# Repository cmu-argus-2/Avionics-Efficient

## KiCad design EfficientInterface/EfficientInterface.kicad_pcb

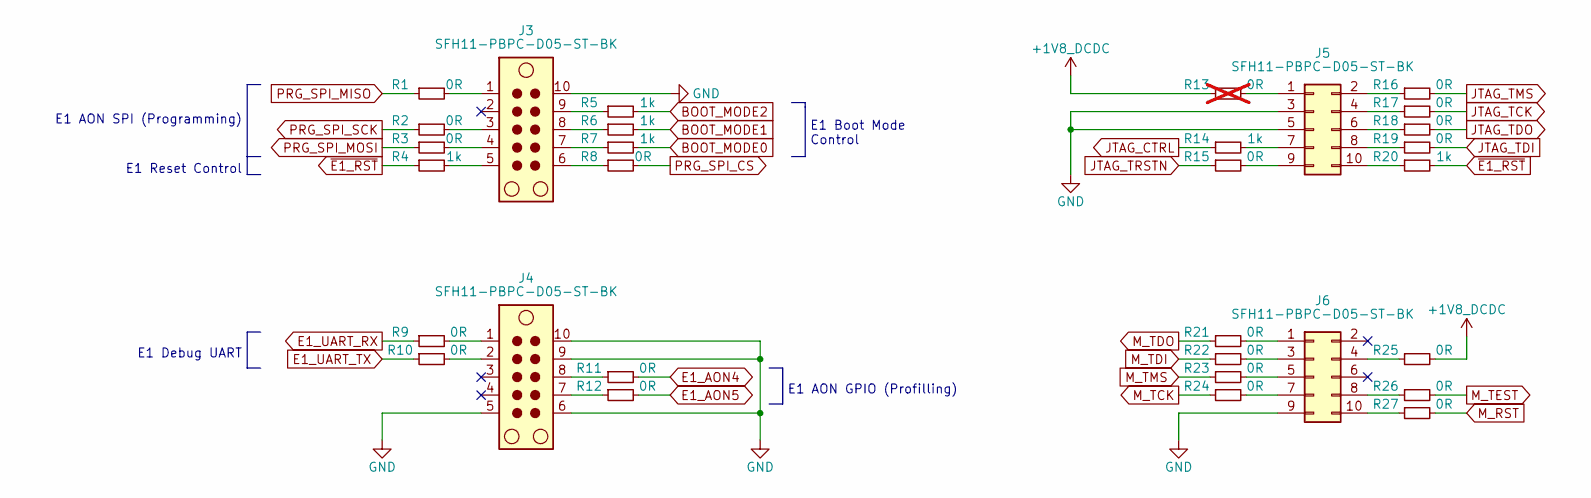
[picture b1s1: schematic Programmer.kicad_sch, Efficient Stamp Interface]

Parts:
J3, J4, J5, J6: SFH11-PBPC-D05-ST-BK; PinSocket_2x05_P2.54mm_Vertical
R1, R2, R3, R8, R9, R10, R11, R12, R15, R16, R17, R18, R19, R21, R22, R23, R24, R25, R26, R27: 0R; R_0603_1608Metric
R4, R5, R6, R7, R14, R20: 1k; R_0603_1608Metric
R13: 0R; R_0603_1608Metric; not fitted

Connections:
+1V8_DCDC: R13.1, R25.2; also elsewhere on the board
BOOT_MODE0: R7.2; also elsewhere on the board
BOOT_MODE1: R6.2; also elsewhere on the board
BOOT_MODE2: R5.2; also elsewhere on the board
DIGIO034_B: R10.1; also elsewhere on the board
DIGIO035_B: R9.1; also elsewhere on the board
E1_AON4: R11.2; also elsewhere on the board
E1_AON5: R12.2; also elsewhere on the board
GND: J3.10, J4.5, J4.6, J4.9, J4.10, J5.3, J5.5, J6.9; also elsewhere on the board
JTAG_CTRL: R14.1; also elsewhere on the board
JTAG_TCK: R17.2; also elsewhere on the board
JTAG_TDI: R19.2; also elsewhere on the board
JTAG_TDO: R18.2; also elsewhere on the board
JTAG_TMS: R16.2; also elsewhere on the board
JTAG_TRSTN: R15.1; also elsewhere on the board
M_RST: R27.2; also elsewhere on the board
M_TCK: R24.1; also elsewhere on the board
M_TDI: R22.1; also elsewhere on the board
M_TDO: R21.1; also elsewhere on the board
M_TEST: R26.2; also elsewhere on the board
M_TMS: R23.1; also elsewhere on the board
unnamed: J3.1, R1.2
unnamed: J3.3, R2.2
unnamed: J3.4, R3.2
unnamed: J3.5, R4.2
unnamed: J3.6, R8.1
unnamed: J3.7, R7.1
unnamed: J3.8, R6.1
unnamed: J3.9, R5.1
unnamed: J4.1, R9.2
unnamed: J4.2, R10.2
unnamed: J4.7, R12.1
unnamed: J4.8, R11.1
unnamed: J5.1, R13.2
unnamed: J5.2, R16.1
unnamed: J5.4, R17.1
unnamed: J5.6, R18.1
unnamed: J5.7, R14.2
unnamed: J5.8, R19.1
unnamed: J5.9, R15.2
unnamed: J5.10, R20.1
unnamed: J6.1, R21.2
unnamed: J6.3, R22.2
unnamed: J6.4, R25.1
unnamed: J6.5, R23.2
unnamed: J6.7, R24.2
unnamed: J6.8, R26.1
unnamed: J6.10, R27.1
PRG_SPI_CS: R8.2; also elsewhere on the board
PRG_SPI_MISO: R1.1; also elsewhere on the board
PRG_SPI_MOSI: R3.1; also elsewhere on the board
PRG_SPI_SCK: R2.1; also elsewhere on the board
~E1_RST: R4.1, R20.2; also elsewhere on the board

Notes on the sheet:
E1 Boot Mode Control
E1 AON SPI (Programming)
E1 AON GPIO (Profilling)
E1 Reset Control
E1 Debug UART

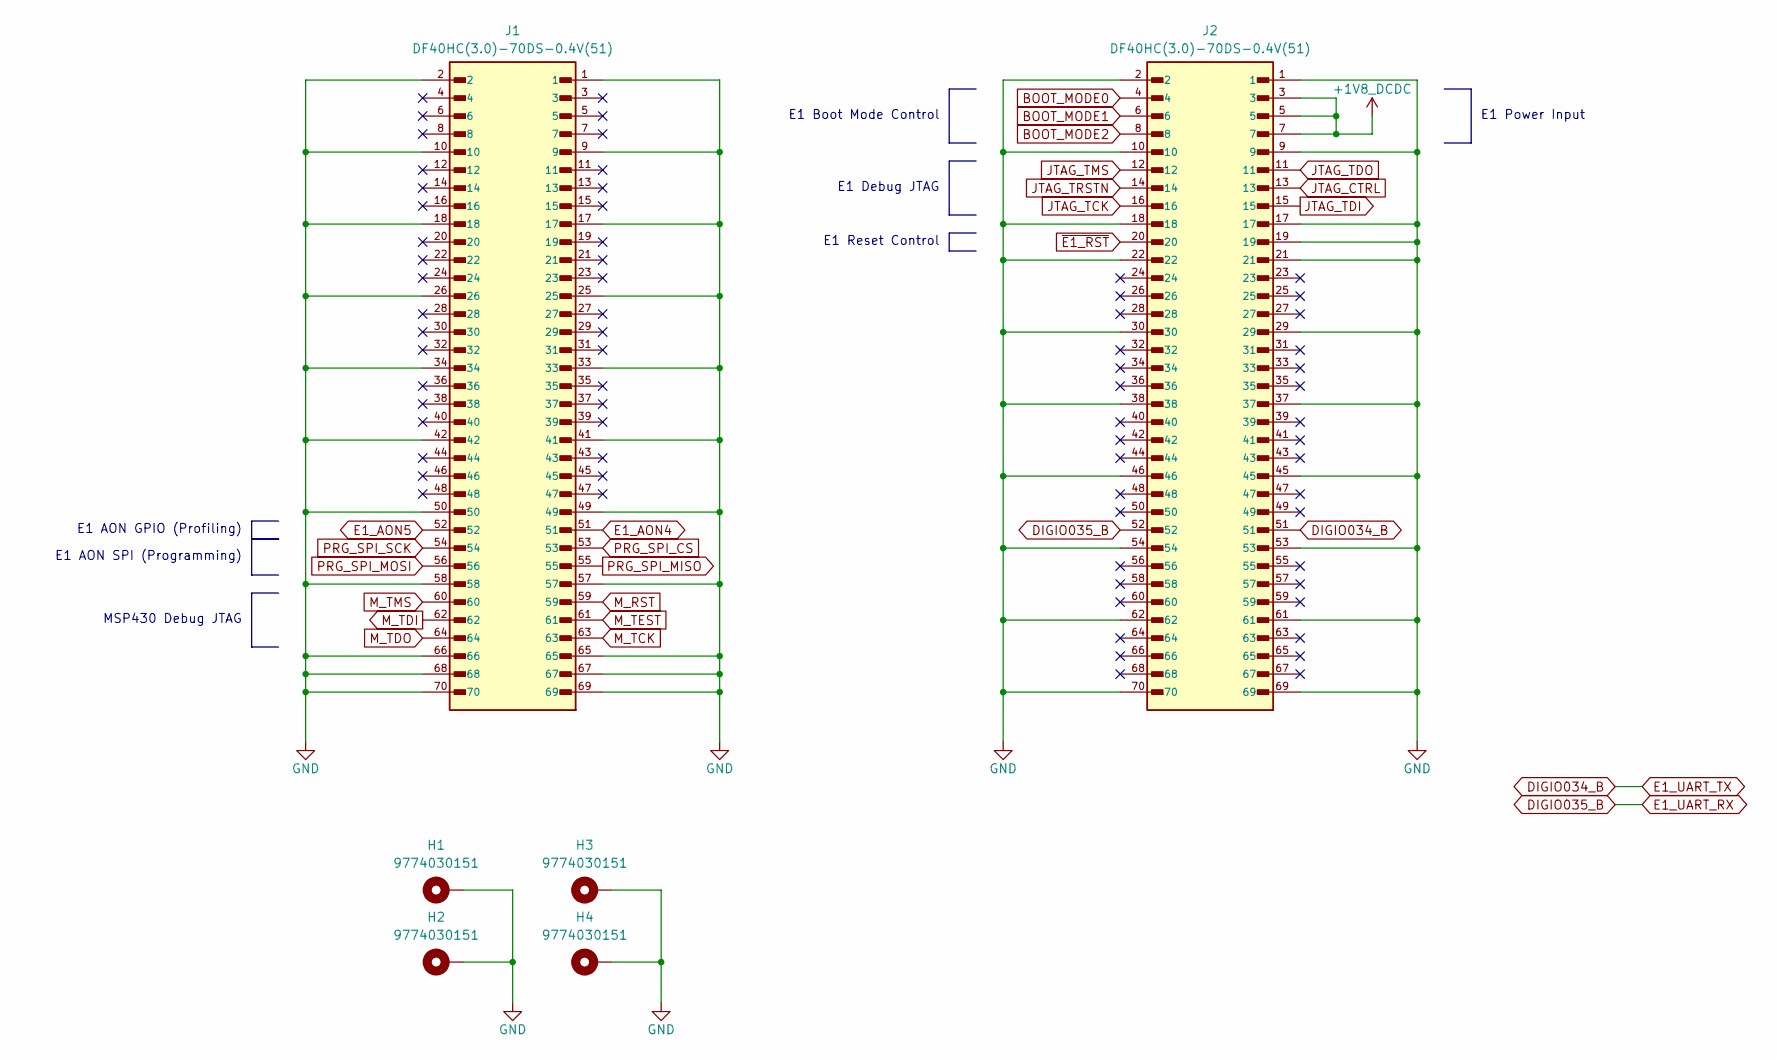
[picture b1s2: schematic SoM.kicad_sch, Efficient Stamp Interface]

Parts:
H1, H2, H3, H4: 9774030151; Mounting_Wuerth_WA-SMSI-M2.5_H3mm_9774030151
J1, J2: DF40HC(3.0)-70DS-0.4V(51); Hirose_DF40C-70DS-0.4V_2x35_P0.4mm

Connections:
+1V8_DCDC: J2.3, J2.5, J2.7; also elsewhere on the board
BOOT_MODE0: J2.4; also elsewhere on the board
BOOT_MODE1: J2.6; also elsewhere on the board
BOOT_MODE2: J2.8; also elsewhere on the board
DIGIO034_B: J2.51; also elsewhere on the board
DIGIO035_B: J2.52; also elsewhere on the board
E1_AON4: J1.51; also elsewhere on the board
E1_AON5: J1.52; also elsewhere on the board
GND: H1.1 (1_1), H2.1 (1_1), H3.1 (1_1), H4.1 (1_1), J1.1, J1.2, J1.9, J1.10, J1.17, J1.18, J1.25, J1.26, J1.33, J1.34, J1.41, J1.42, J1.49, J1.50, J1.57, J1.58, J1.65, J1.66, J1.67, J1.68, J1.69, J1.70, J2.1, J2.2, J2.9, J2.10, J2.17, J2.18, J2.19, J2.21, J2.22, J2.29, J2.30, J2.37, J2.38, J2.45, J2.46, J2.53, J2.54, J2.61, J2.62, J2.69, J2.70; also elsewhere on the board
JTAG_CTRL: J2.13; also elsewhere on the board
JTAG_TCK: J2.16; also elsewhere on the board
JTAG_TDI: J2.15; also elsewhere on the board
JTAG_TDO: J2.11; also elsewhere on the board
JTAG_TMS: J2.12; also elsewhere on the board
JTAG_TRSTN: J2.14; also elsewhere on the board
M_RST: J1.59; also elsewhere on the board
M_TCK: J1.63; also elsewhere on the board
M_TDI: J1.62; also elsewhere on the board
M_TDO: J1.64; also elsewhere on the board
M_TEST: J1.61; also elsewhere on the board
M_TMS: J1.60; also elsewhere on the board
PRG_SPI_CS: J1.53; also elsewhere on the board
PRG_SPI_MISO: J1.55; also elsewhere on the board
PRG_SPI_MOSI: J1.56; also elsewhere on the board
PRG_SPI_SCK: J1.54; also elsewhere on the board
~E1_RST: J2.20; also elsewhere on the board

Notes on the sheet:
E1 AON SPI (Programming)
E1 Boot Mode Control
E1 Reset Control
E1 AON GPIO (Profiling)
E1 Debug JTAG
MSP430 Debug JTAG
E1 Power Input

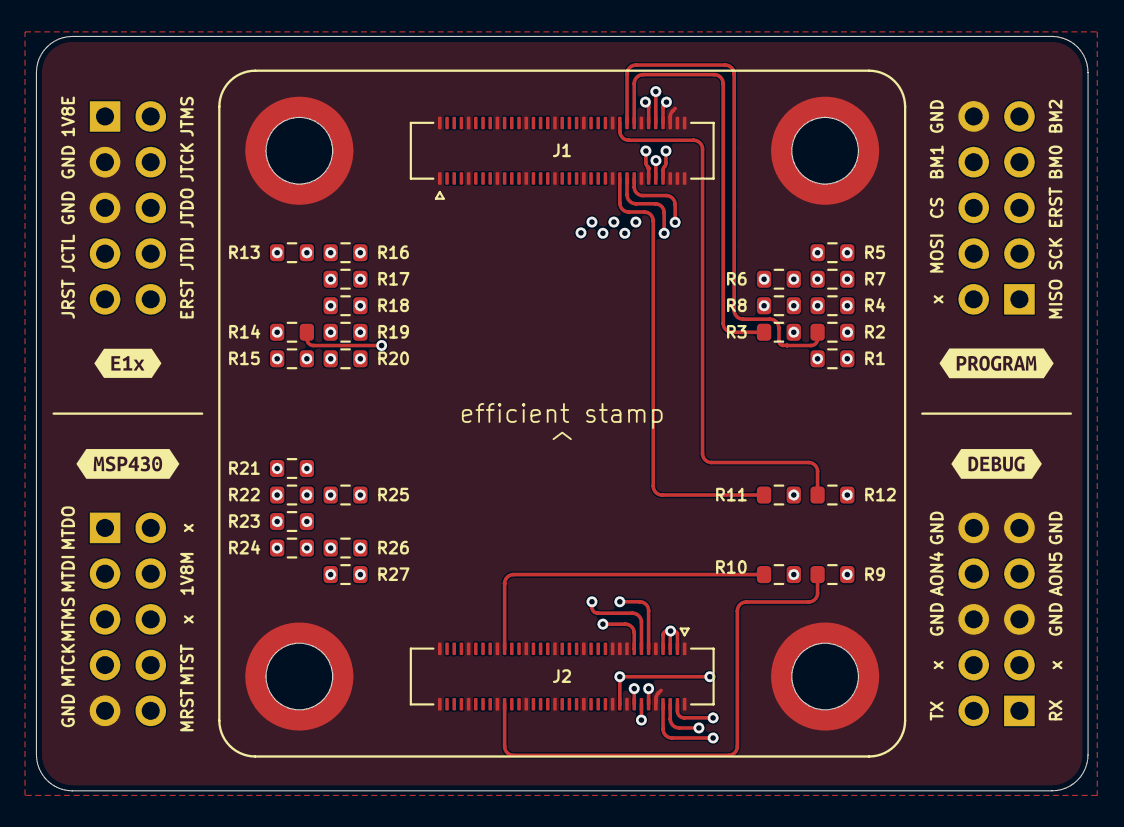
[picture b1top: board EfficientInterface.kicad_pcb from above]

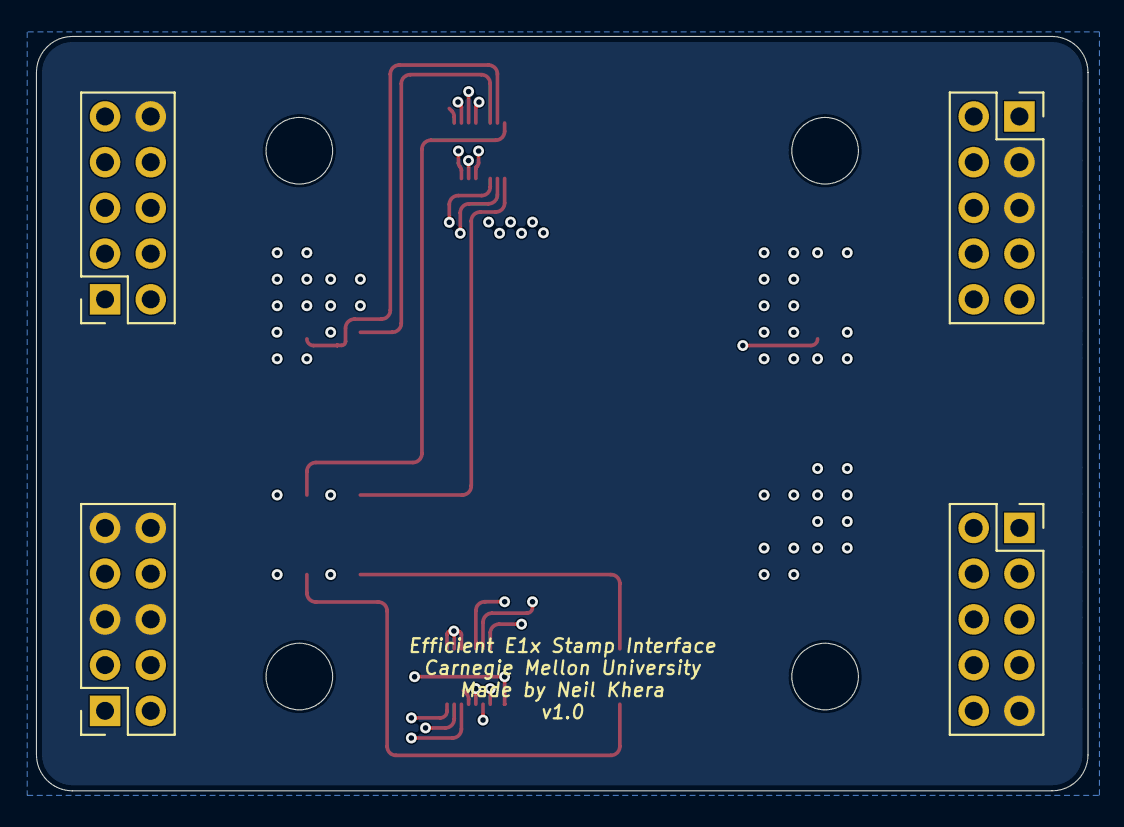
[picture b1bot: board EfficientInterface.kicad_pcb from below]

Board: 4 copper layers, 58.4 x 41.9 mm, 41 parts (4 on the bottom side), 53 nets.

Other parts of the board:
kibuzzard-6A03C779: G***; kibuzzard-6A03C779
kibuzzard-6A03E4CB: G***; kibuzzard-6A03E4CB
kibuzzard-6A03EEF0: G***; kibuzzard-6A03EEF0
kibuzzard-6A0274B3: G***; kibuzzard-6A0274B3

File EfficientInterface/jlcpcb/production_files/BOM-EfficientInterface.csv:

Comment,Designator,Footprint,LCSC,Quantity
0R,"R1,R10,R11,R12,R15,R16,R17,R18,R19,R2,R21,R22,R23,R24,R25,R26,R27,R3,R8,R9",R_0603_1608Metric,C2441282,20
1k,"R14,R20,R4,R5,R6,R7",R_0603_1608Metric,C2484691,6
DF40HC(3.0)-70DS-0.4V(51),"J1,J2",Hirose_DF40C-70DS-0.4V_2x35_P0.4mm,C597944,2
SFH11-PBPC-D05-ST-BK,J3,PinSocket_2x05_P2.54mm_Vertical,,1
SFH11-PBPC-D05-ST-BK,J5,PinSocket_2x05_P2.54mm_Vertical,,1
SFH11-PBPC-D05-ST-BK,J6,PinSocket_2x05_P2.54mm_Vertical,,1
SFH11-PBPC-D05-ST-BK,J4,PinSocket_2x05_P2.54mm_Vertical,,1

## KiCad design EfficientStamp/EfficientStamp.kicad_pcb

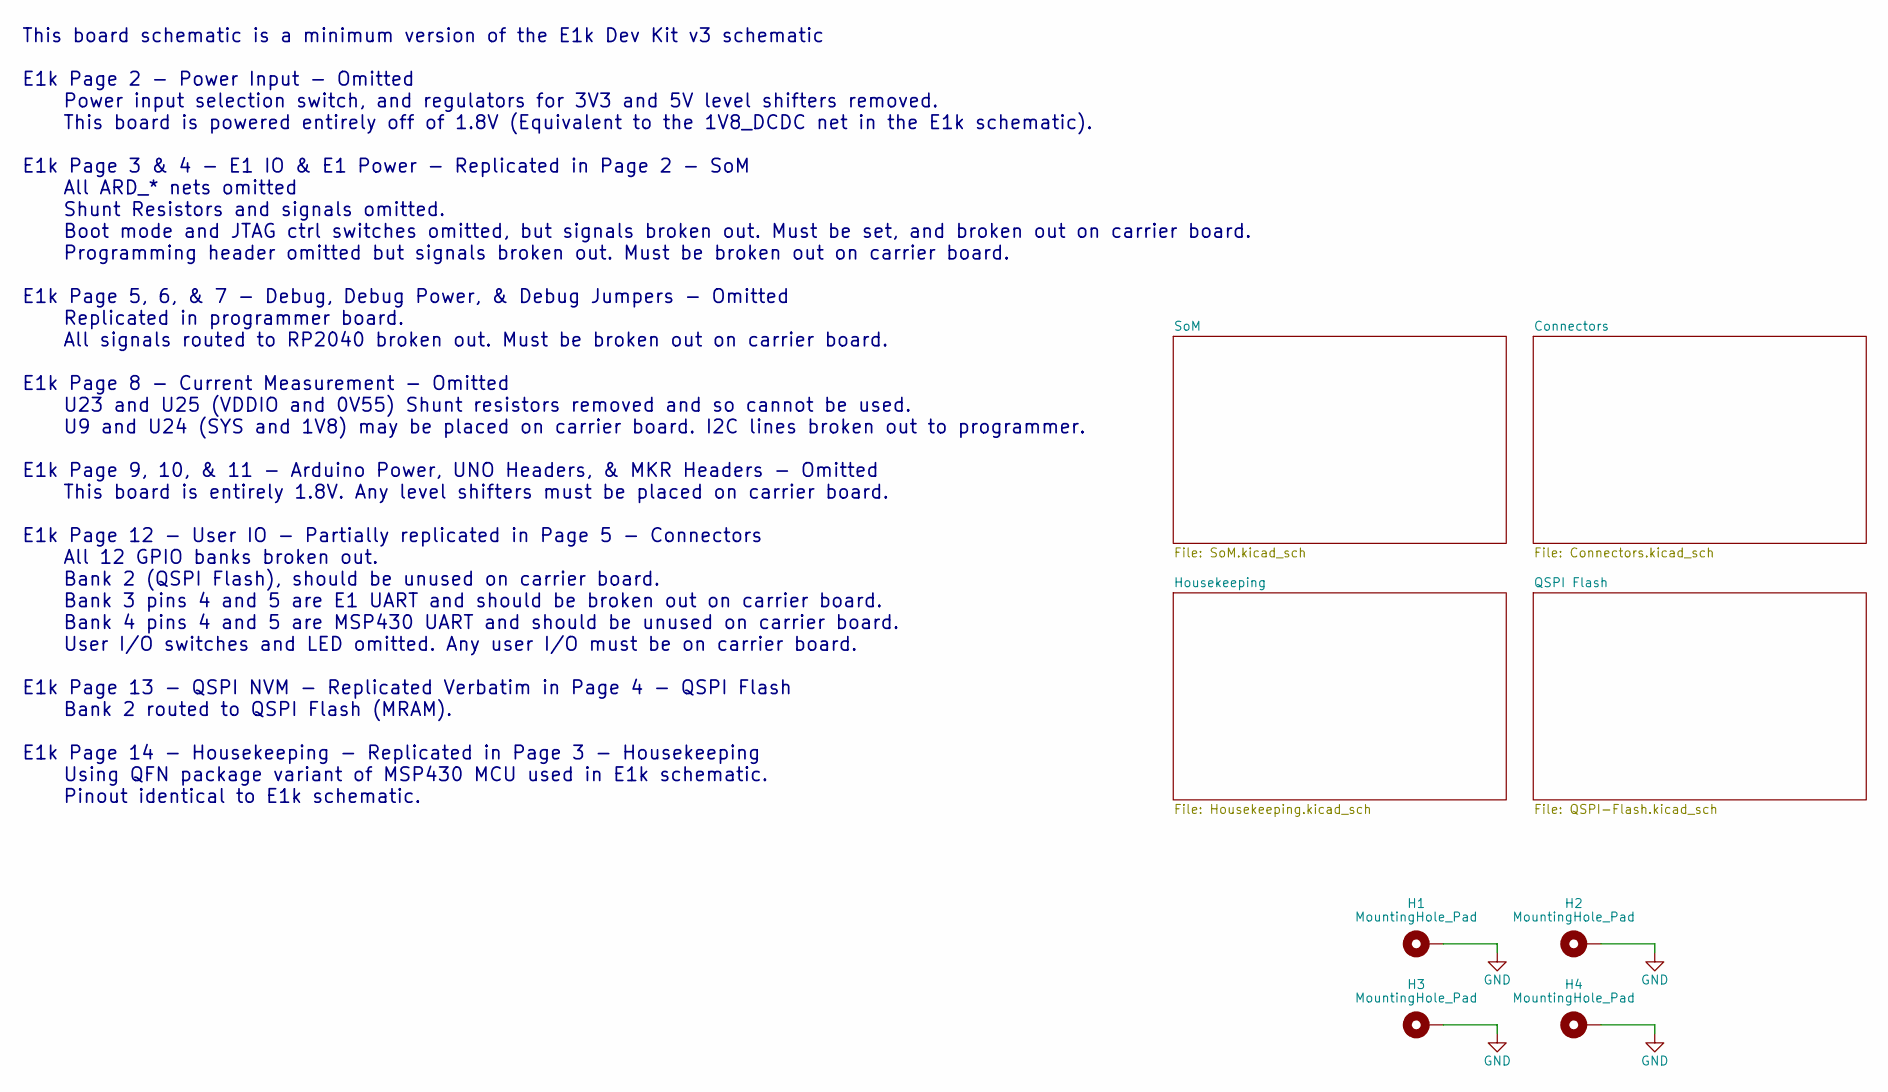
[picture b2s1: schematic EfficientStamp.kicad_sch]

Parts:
H1, H2, H3, H4: MountingHole_Pad; MountingHole_2.7mm_M2.5_DIN965_Pad

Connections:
GND: H1.1 (1_1), H2.1 (1_1), H3.1 (1_1), H4.1 (1_1); also elsewhere on the board

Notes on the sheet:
This board schematic is a minimum version of the E1k Dev Kit v3 schematic E1k Page 2 - Power Input - Omitted Power input selection switch, and regulators for 3V3 and 5V level shifters removed. This board is powered entirely off of 1.8V (Equivalent to the 1V8_DCDC net in the E1k schematic). E1k Page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

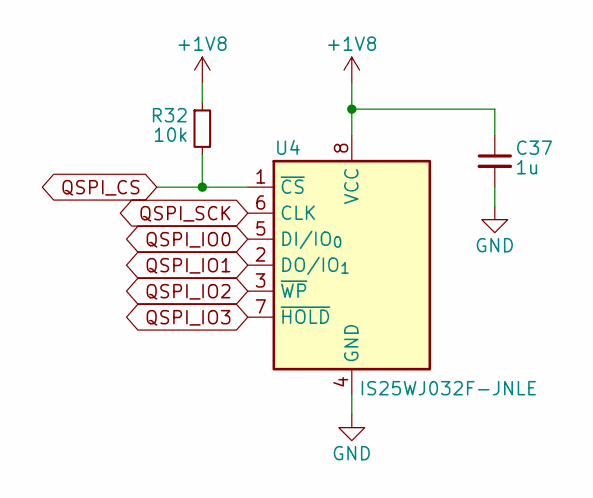
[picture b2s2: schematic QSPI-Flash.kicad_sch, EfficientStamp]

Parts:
C37: 1u; C_0402_1005Metric
R32: 10k; R_0402_1005Metric
U4: IS25WJ032F-JNLE; SOIC-8_3.9x4.9mm_P1.27mm

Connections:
+1V8: C37.1, R32.1, U4.8 (VCC); also elsewhere on the board
DIGIO010_B: U4.6 (CLK); also elsewhere on the board
DIGIO011_B: R32.2, U4.1 (~CS); also elsewhere on the board
DIGIO012_B: U4.5 (DI/IO_{0}); also elsewhere on the board
DIGIO013_B: U4.2 (DO/IO_{1}); also elsewhere on the board
DIGIO014_B: U4.3 (~WP); also elsewhere on the board
DIGIO015_B: U4.7 (~HOLD); also elsewhere on the board
GND: C37.2, U4.4 (GND); also elsewhere on the board

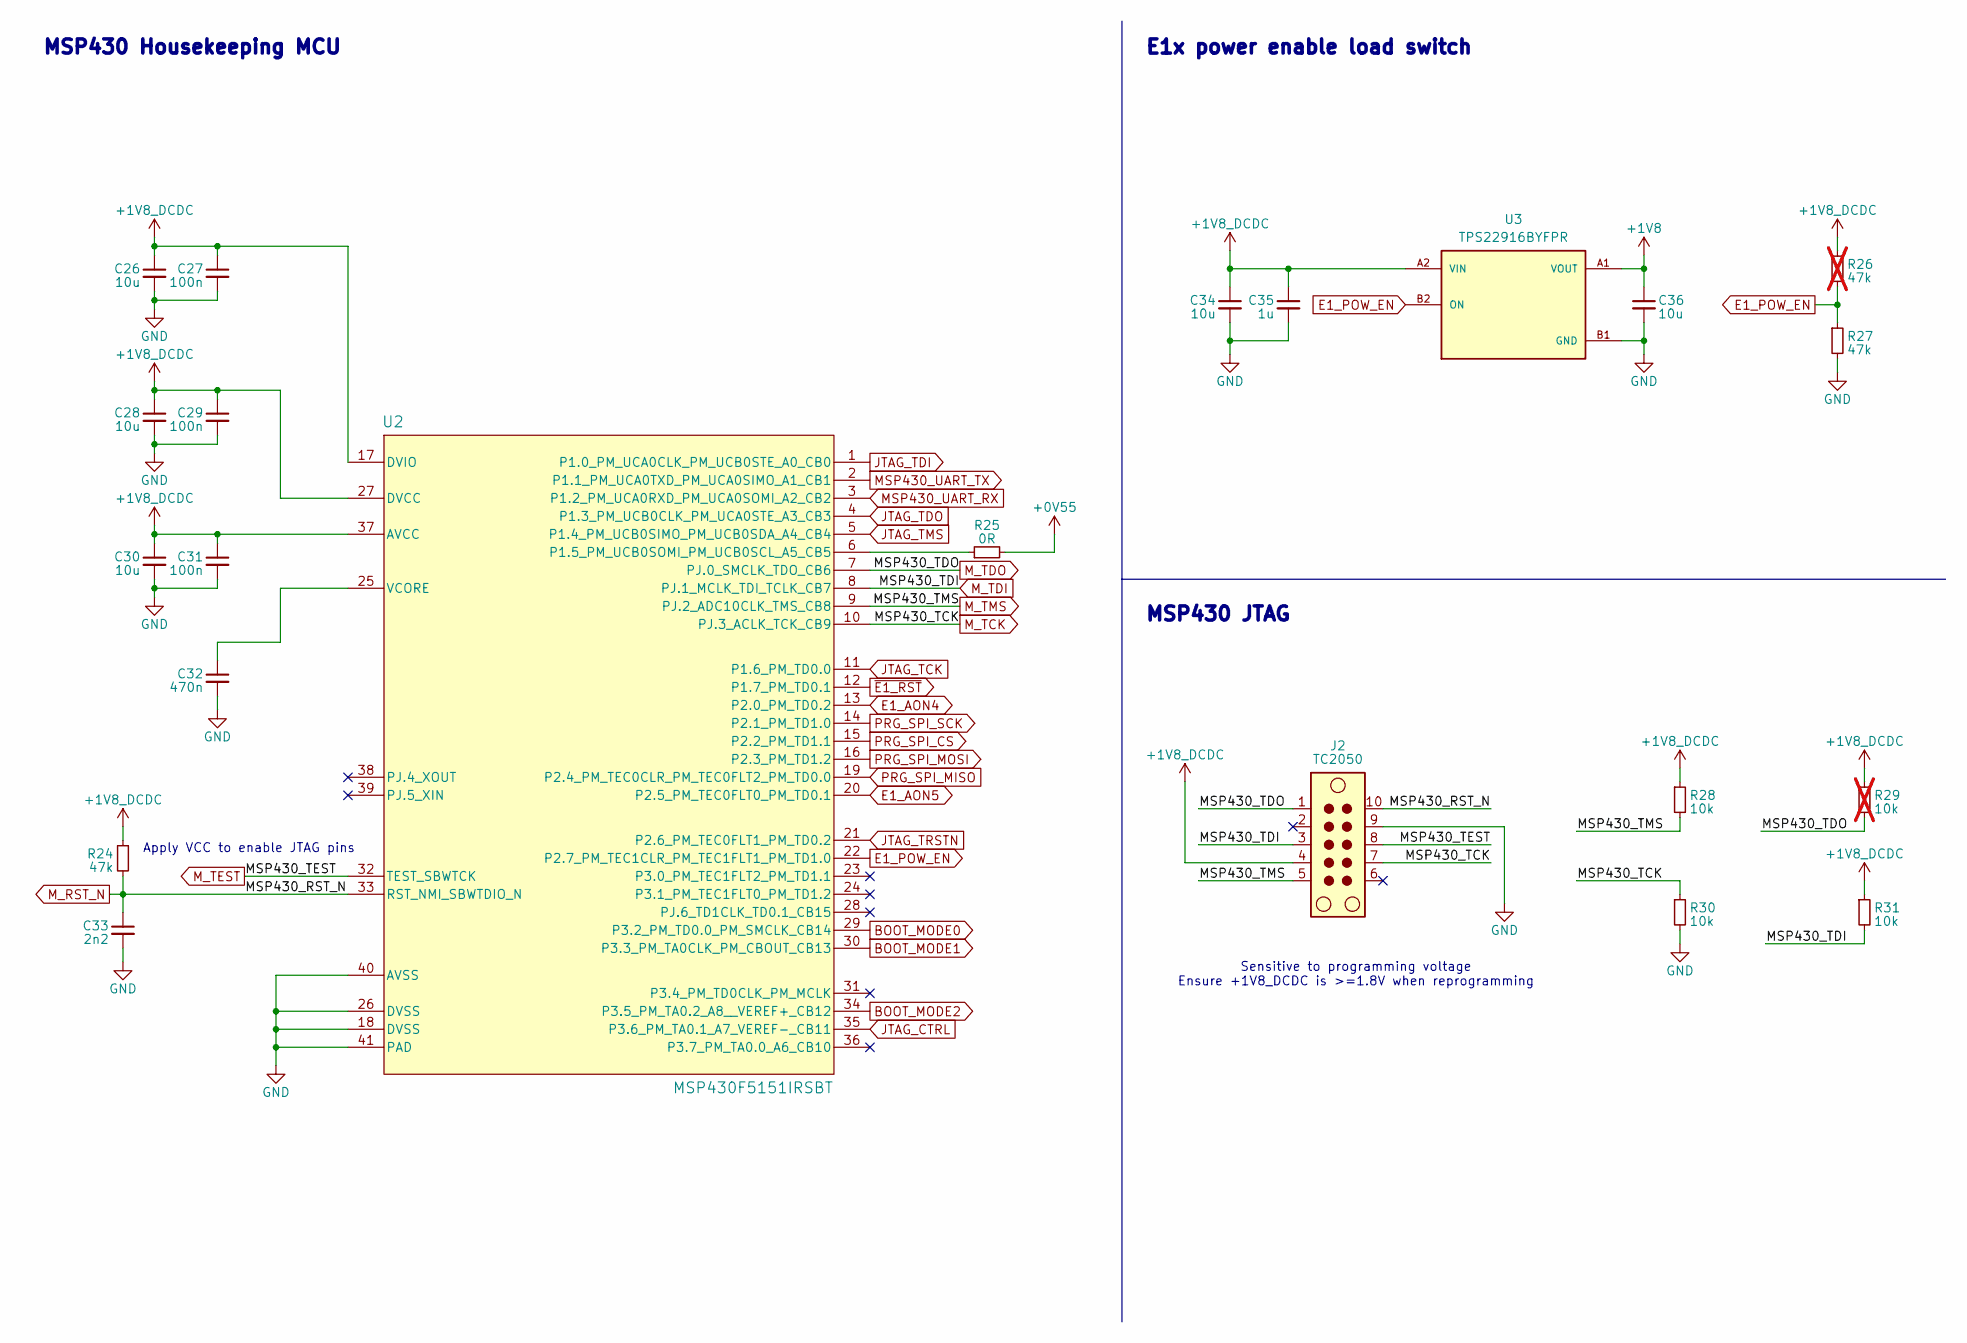
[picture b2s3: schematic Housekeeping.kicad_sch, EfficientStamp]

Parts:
C26, C28, C30, C34, C36: 10u; C_0402_1005Metric
C27, C29, C31: 100n; C_0402_1005Metric
C32: 470n; C_0402_1005Metric
C33: 2n2; C_0402_1005Metric
C35: 1u; C_0402_1005Metric
J2: TC2050; Tag-Connect_TC2050-IDC-NL_2x05_P1.27mm_Vertical
R24, R27: 47k; R_0402_1005Metric
R25: 0R; R_0402_1005Metric
R26: 47k; R_0402_1005Metric; not fitted
R28, R30, R31: 10k; R_0402_1005Metric
R29: 10k; R_0402_1005Metric; not fitted
U2: MSP430F5151IRSBT; VQFN-40-1EP_5x5mm_P0.4mm_EP3.6x3.6mm
U3: TPS22916BYFPR; Texas_PicoStar_BGA-4_0.758x0.758mm_Layout2x2_P0.4mm

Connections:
+0V55: R25.2; also elsewhere on the board
+1V8: C36.1, U3.A1 (VOUT); also elsewhere on the board
+1V8_DCDC: C26.1, C27.1, C28.1, C29.1, C30.1, C31.1, C34.1, C35.1, J2.4, R24.1, R26.1, R28.1, R29.1, R31.1, U2.17 (DVIO), U2.27 (DVCC), U2.37 (AVCC), U3.A2 (VIN); also elsewhere on the board
BOOT_MODE0: U2.29 (P3.2_PM_TD0.0_PM_SMCLK_CB14); also elsewhere on the board
BOOT_MODE1: U2.30 (P3.3_PM_TA0CLK_PM_CBOUT_CB13); also elsewhere on the board
BOOT_MODE2: U2.34 (P3.5_PM_TA0.2_A8__VEREF+_CB12); also elsewhere on the board
DIGIO044_B: U2.3 (P1.2_PM_UCA0RXD_PM_UCA0SOMI_A2_CB2); also elsewhere on the board
DIGIO045_B: U2.2 (P1.1_PM_UCA0TXD_PM_UCA0SIMO_A1_CB1); also elsewhere on the board
E1_AON4: U2.13 (P2.0_PM_TD0.2); also elsewhere on the board
E1_AON5: U2.20 (P2.5_PM_TEC0FLT0_PM_TD0.1); also elsewhere on the board
E1_POW_EN: R26.2, R27.1, U2.22 (P2.7_PM_TEC1CLR_PM_TEC1FLT1_PM_TD1.0), U3.B2 (ON)
GND: C26.2, C27.2, C28.2, C29.2, C30.2, C31.2, C32.2, C33.2, C34.2, C35.2, C36.2, J2.9, R27.2, R30.2, U2.18 (DVSS), U2.26 (DVSS), U2.40 (AVSS), U2.41 (PAD), U3.B1 (GND); also elsewhere on the board
JTAG_CTRL: U2.35 (P3.6_PM_TA0.1_A7_VEREF-_CB11); also elsewhere on the board
JTAG_TCK: U2.11 (P1.6_PM_TD0.0); also elsewhere on the board
JTAG_TDI: U2.1 (P1.0_PM_UCA0CLK_PM_UCB0STE_A0_CB0); also elsewhere on the board
JTAG_TDO: U2.4 (P1.3_PM_UCB0CLK_PM_UCA0STE_A3_CB3); also elsewhere on the board
JTAG_TMS: U2.5 (P1.4_PM_UCB0SIMO_PM_UCB0SDA_A4_CB4); also elsewhere on the board
JTAG_TRSTN: U2.21 (P2.6_PM_TEC0FLT1_PM_TD0.2); also elsewhere on the board
M_RST_N: C33.1, J2.10, R24.2, U2.33 (RST_NMI_SBWTDIO_N); also elsewhere on the board
M_TCK: J2.7, R30.1, U2.10 (PJ.3_ACLK_TCK_CB9); also elsewhere on the board
M_TDI: J2.3, R31.2, U2.8 (PJ.1_MCLK_TDI_TCLK_CB7); also elsewhere on the board
M_TDO: J2.1, R29.2, U2.7 (PJ.0_SMCLK_TDO_CB6); also elsewhere on the board
M_TEST: J2.8, U2.32 (TEST_SBWTCK); also elsewhere on the board
M_TMS: J2.5, R28.2, U2.9 (PJ.2_ADC10CLK_TMS_CB8); also elsewhere on the board
unnamed: R25.1, U2.6 (P1.5_PM_UCB0SOMI_PM_UCB0SCL_A5_CB5)
unnamed: C32.1, U2.25 (VCORE)
PRG_SPI_CS: U2.15 (P2.2_PM_TD1.1); also elsewhere on the board
PRG_SPI_MISO: U2.19 (P2.4_PM_TEC0CLR_PM_TEC0FLT2_PM_TD0.0); also elsewhere on the board
PRG_SPI_MOSI: U2.16 (P2.3_PM_TD1.2); also elsewhere on the board
PRG_SPI_SCK: U2.14 (P2.1_PM_TD1.0); also elsewhere on the board
~E1_RST: U2.12 (P1.7_PM_TD0.1); also elsewhere on the board

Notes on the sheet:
MSP430 JTAG
E1x power enable load switch
MSP430 Housekeeping MCU
Sensitive to programming voltage Ensure +1V8_DCDC is >=1.8V when reprogramming
Apply VCC to enable JTAG pins

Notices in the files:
parts and their libraries:
License: Apache-2.0
